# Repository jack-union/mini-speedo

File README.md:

# mini-speedo
Electronic Speedo for classic minis

Using an Arduino Nano v3, a SSD1306 0,96" 128x64 display and a GM X27.168 stepper motor.

Featuring a multifunction display for:
* total distance
* trip distance
* digital speed
* lambda (AFR)
* oil temperature
* oil pressure
* voltage
* water temperature
* external temperature
* rpm

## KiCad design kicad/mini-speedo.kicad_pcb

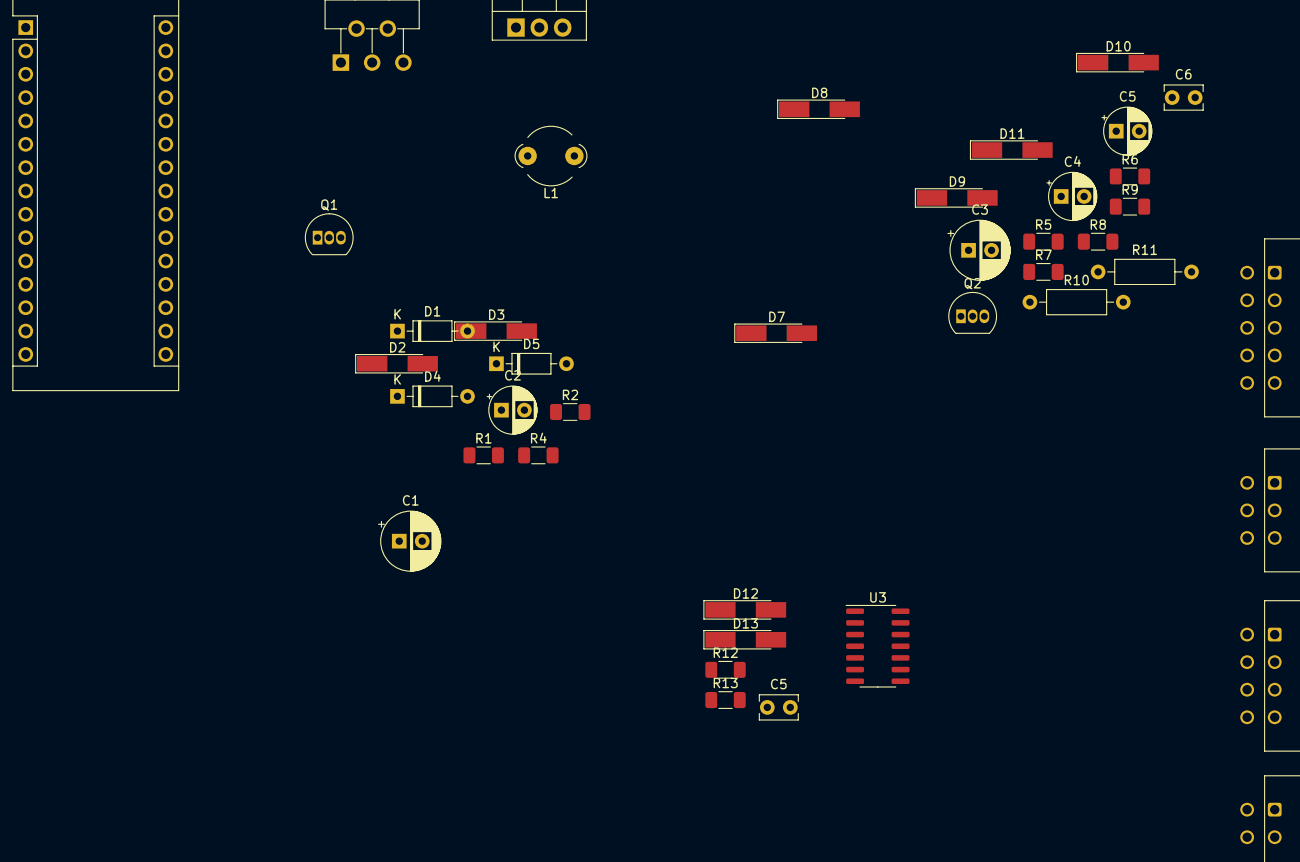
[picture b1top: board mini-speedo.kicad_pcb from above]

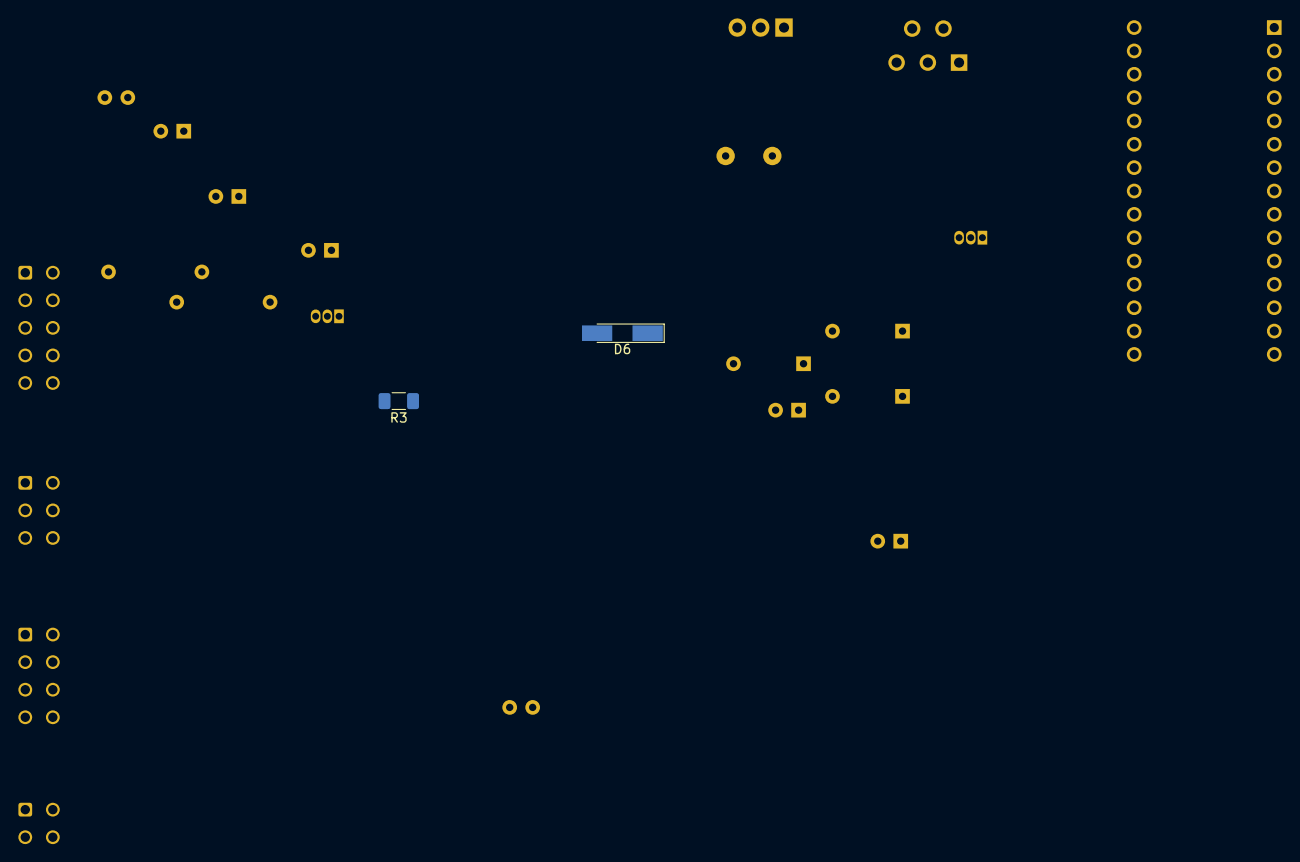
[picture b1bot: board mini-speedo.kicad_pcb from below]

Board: 2 copper layers, 44 parts (2 on the bottom side), 34 nets, no tracks yet.

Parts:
A1: Arduino; Arduino_Nano
C1, C3: 47uF; CP_Radial_D6.3mm_P2.50mm
C2, C4: 33uF; CP_Radial_D5.0mm_P2.50mm
C5: 10uF; CP_Radial_D5.0mm_P2.50mm
C5#2: 10nF; C_Rect_L4.0mm_W2.5mm_P2.50mm
C6: 33nF; C_Rect_L4.0mm_W2.5mm_P2.50mm
D1: D_Schottky; D_DO-35_SOD27_P7.62mm_Horizontal
D2, D3, D6, D7, D8, D9, D10, D11, D12, D13: 4.7V; D_MiniMELF_Handsoldering
D4, D5: 1N4148; D_DO-35_SOD27_P7.62mm_Horizontal
J1: Conn_01x06; Molex_Micro-Fit_3.0_43045-0600_2x03_P3.00mm_Horizontal
J2: Conn_01x08; Molex_Micro-Fit_3.0_43045-0800_2x04_P3.00mm_Horizontal
J3: Conn_01x10; Molex_Micro-Fit_3.0_43045-1000_2x05_P3.00mm_Horizontal
J4: Conn_01x04; Molex_Micro-Fit_3.0_43045-0400_2x02_P3.00mm_Horizontal
L1: 33uH; LairdTech_28C0236-0JW-10
Q1, Q2: BC546; TO-92_Inline
R1, R2, R3, R4, R6, R7, R8, R13: 10k; R_1206_3216Metric_Pad1.30x1.75mm_HandSolder
R5: 30k; R_1206_3216Metric_Pad1.30x1.75mm_HandSolder
R9: 1k; R_1206_3216Metric_Pad1.30x1.75mm_HandSolder
R10: 100; R_Axial_DIN0207_L6.3mm_D2.5mm_P10.16mm_Horizontal
R11: 470; R_Axial_DIN0207_L6.3mm_D2.5mm_P10.16mm_Horizontal
R12: 15k; R_1206_3216Metric_Pad1.30x1.75mm_HandSolder
U1: LM2596T-5; TO-220-5_P3.4x3.7mm_StaggerOdd_Lead3.8mm_Vertical
U2: LM7810_TO220; TO-220-3_Vertical
U3: 74HC14; SO-14_3.9x8.65mm_P1.27mm

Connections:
GND: A1.4, A1.29, C1.2, C2.2, C3.2, C4.2, C5.2, C5#2.2, C6.2, D1.2, D2.2, D3.2, D6.2, D7.2, D8.2, D9.2, D10.2, D11.2, D13.2, J1.6, J2.8, J3.2, J4.4, Q1.3, Q2.3, R6.1, R7.1, R13.1, U1.3, U2.2, U3.7
unnamed: A1.5, D8.1, R9.1
unnamed: A1.6, U3.2
unnamed: A1.7, J2.1
unnamed: A1.8, J2.2
unnamed: A1.9, J2.3
unnamed: A1.10, J2.4
unnamed: A1.13, D4.2
unnamed: A1.14, D2.1, R4.1
unnamed: A1.15, D5.1
unnamed: A1.16, R3.1
unnamed: A1.19, J3.3
unnamed: A1.20, D11.1, J3.5, R11.1
unnamed: A1.21, D10.1, J3.6, R10.1
unnamed: A1.22, D9.1, J3.7
unnamed: A1.23, J2.6
unnamed: A1.24, J2.7
unnamed: A1.25, C6.1, D7.1, R7.2, R8.1
unnamed: A1.26, C5.1, D6.1, R5.1, R6.2
unnamed: A1.27, C2.1, D12.1, J2.5, J3.1, L1.1, R10.2, R11.2, U1.4, U3.14
unnamed: C1.1, J1.1, U1.1
unnamed: C3.1, J1.2, J4.2, R1.2, R4.2, R5.2, U2.1
unnamed: C4.1, J1.3, U2.3
unnamed: C5#2.1, D12.2, D13.1, R12.1, R13.2
unnamed: D1.1, L1.2, U1.2
unnamed: D3.1, D5.2, R2.1, U1.5
unnamed: D4.1, J1.4
unnamed: J1.5, Q2.1
unnamed: J3.4, R8.2
unnamed: J4.1, R12.2
unnamed: J4.3, R9.2
unnamed: Q1.1, R2.2
unnamed: Q1.2, R1.1
unnamed: Q2.2, R3.2

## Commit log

2020-08-24 Initial commit, display code.
2020-08-24 Renamed file due to Arduino IDE
2020-08-24 input definitions cleanup, created interrupt handling
2020-08-24 little cleanup, stepper code reactivated
2020-08-24 cleanup, trip display with less ifs
2020-08-27 interrupt handling, rpm and speed data handling started
2020-08-27 rpm not volatile
2020-08-27 RPM code working, no circular buffer for RPM.
2020-08-27 Update stepper in main loop, asynchronously.
2020-08-27 speed is hard, distance is harder...
2020-08-28 distances in meters, adapted display accordingly. corrected distance calculations. explicitly stated units. added rollover code for 100000km display.
2020-08-28 calm speed reading
2020-08-28 Speedo stepper code, first shot.
2020-08-28 limit speedo needle travel to max steps
2020-08-28 fixes ROLLOVER definition
2020-08-28 make startup needle sweep an option
2020-08-28 fixes integer overflow
2020-08-28 EEPROM load and save code.
2020-08-29 EEPROM: write explicit zeros on first start
2020-08-29 stop code as function
2020-08-29 kicad schematics added, first incomplete version
2020-08-29 code split into multiple files for better overview.
2020-08-29 more file reorganisation
2020-08-29 little cleanups
2020-08-29 Mini van logo variant added
2020-08-30 explained stepper pins better
2020-08-30 set max stepper position according to speedo scale
2020-08-30 Nicer fonts, updates all display functions. Fine tuning max stepper travel.
2020-09-23 Further tests with kicad.
2020-09-23 used watchdog to reset Arduino when power is restored quickly.
2020-09-24 pin assignment for serial lambda and warn output
2020-10-21 added image
2020-11-01 Logo in XBM file format
2020-11-01 KiCad changes, first prototype
2020-11-01 Rewrite of display code to U8g2 library. Changed Logos to XBM format.
2020-11-02 Changed Profont to Logisoso font
2020-11-02 Sorted custom settings to top of main file
2020-11-02 Analog value calculations for lambda and voltage
2020-11-09 Added warning symbol bitmap
2020-11-09 Added code for checking warning limits and display warning symbol
2020-11-09 set oil pressure warning from begin, so display doesn't switch at startup
2020-11-14 Pin swaps for software serial
2020-11-14 Upper limit for voltage reading
2020-11-14 Set warning output pin when warning is active
2020-11-14 Fixes goodbye drawing (u8g2 loop)
2020-11-14 Little more time before shutdown
2020-11-14 Fine tuned stepper max position
2020-11-16 voltage and lambda demodata removed
2020-11-16 AltSerial include for lambda serial input
2020-11-16 Digital sensor DS18B20 reading for outside temperature
2020-11-16 switched to leaner DS18B20_INT library
2020-12-05 Test with full DallasTemperature library
2020-12-05 Compute oil pressure
2020-12-05 print oil pressure as -.-- when sensor not connected
2020-12-05 use NODATA as marker for unavailable sensor data
2020-12-12 Added constants for analog sensors. Multiple runs for analog samples to smooth data.
2020-12-13 More constants for sensor readings
2020-12-13 disable digital temp sensor for the moment...
2020-12-13 Statistics for main loop
2020-12-13 Thermistor temperature floating point calculations and display updates.
2020-12-15 Little cleanups, reduce resolution for Dallas temperature sensor
2020-12-15 replaced several constants with #defines
2020-12-15 switched inputs, removed altSoftSerial temporarily, included DallasTemperature
2020-12-15 optimized logo size
2020-12-15 Dallas temperature reading for outside temp. Changed to 0.5 degrees resolution.
2020-12-16 Trying two display pages in RAM, faster, but more RAM needed.
2020-12-16 reduced memory footprint by using reduced small font.
2020-12-17 switched logo to van
2020-12-17 Added AltSerial dummy code for testing object memory footprint
2020-12-17 U8g2 library memory optimization
2020-12-17 prepared dual display setup
2020-12-18 cleaner startup code
2020-12-18 minor formatting...
2020-12-18 shaved some RAM by using F() macro.
2020-12-18 Big changes to dual display setup. :D
2020-12-20 two identical displays...
2021-01-05 Schematics update, still not finished
2021-03-19 autoformatted by new IDE
2021-03-19 type definition corrected
